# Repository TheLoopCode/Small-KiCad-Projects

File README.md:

# Small-KiCad-Projects

This was developed over 2 months and many hours of testing to provide me with experience going from Schematic to Breadboarding to PCB.

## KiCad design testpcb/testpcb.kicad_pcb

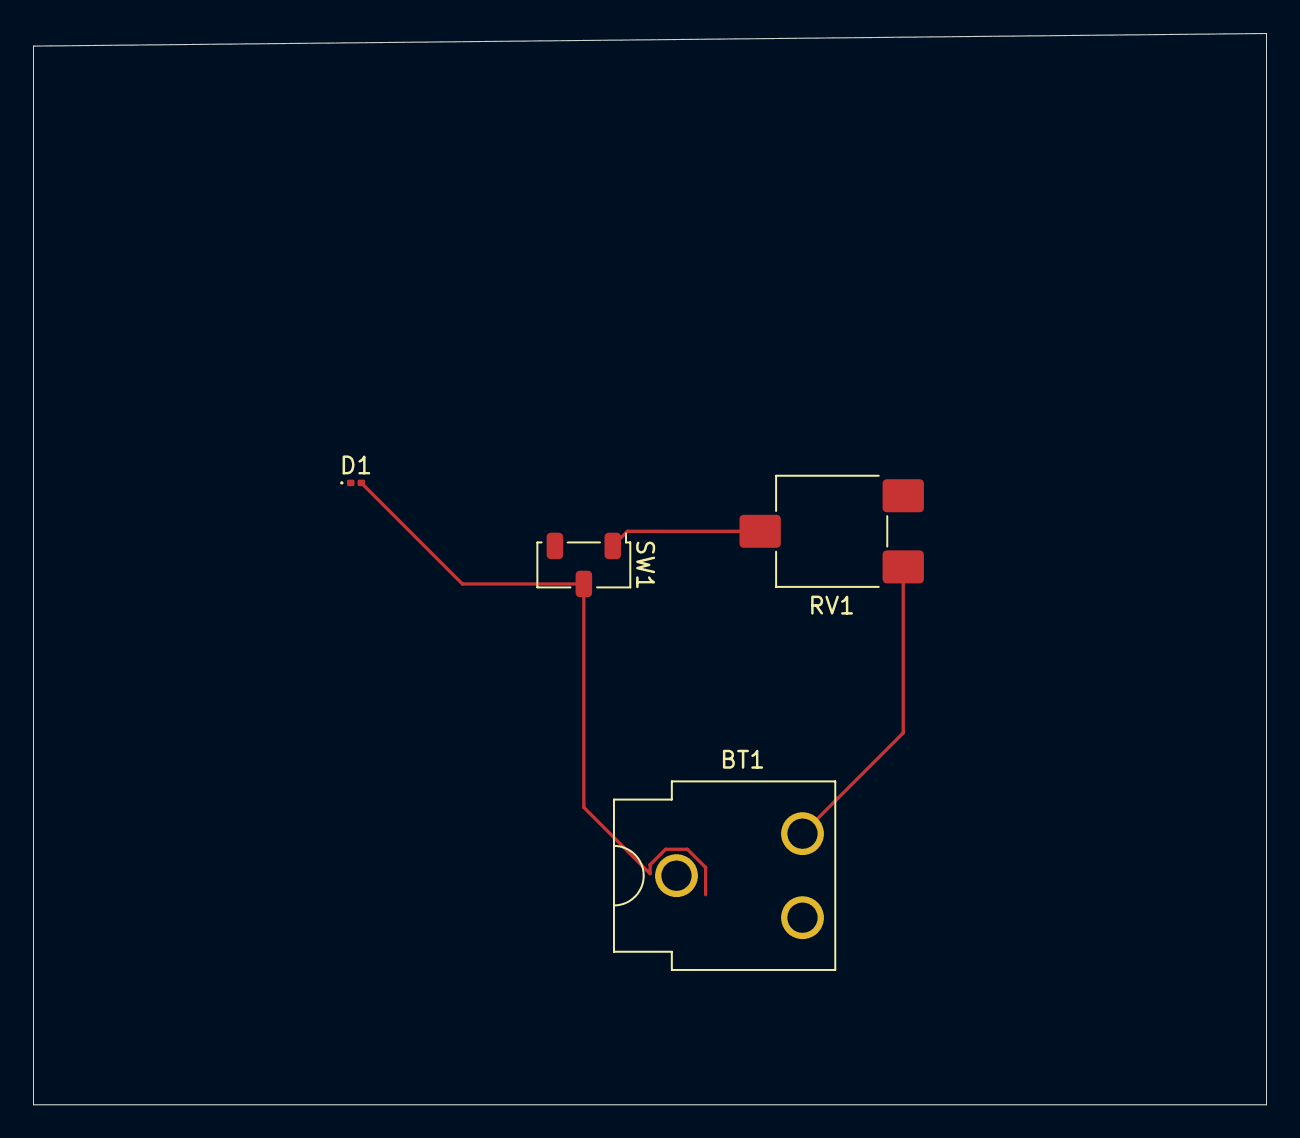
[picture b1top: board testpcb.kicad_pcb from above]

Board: 2 copper layers, 74.5 x 64.8 mm, 4 parts (0 on the bottom side), 3 nets.

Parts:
BT1: Battery; BatteryClip_Keystone_54_D16-19mm
D1: LED; LED_0201_0603Metric
RV1: R_Potentiometer_US; Potentiometer_ACP_CA6-VSMD_Vertical
SW1: SW_Push; Nidec_Copal_CAS-120A

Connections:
+5V: BT1.1 (+_1), RV1.3
GND: D1.2 (A_2), SW1.2
unnamed: RV1.2, SW1.1
